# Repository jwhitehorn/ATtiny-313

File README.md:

#Overview

Open design for a ATtiny2313/4313 development platform.

Inspired by:

[BB-313](http://www.johngineer.com/projects/bb313/)

#License
Designs copyright 2013, Jason Whitehorn released under the terms of:

[Creative Commons CC-BY-SA 3.0](http://creativecommons.org/licenses/by-sa/3.0/us/)

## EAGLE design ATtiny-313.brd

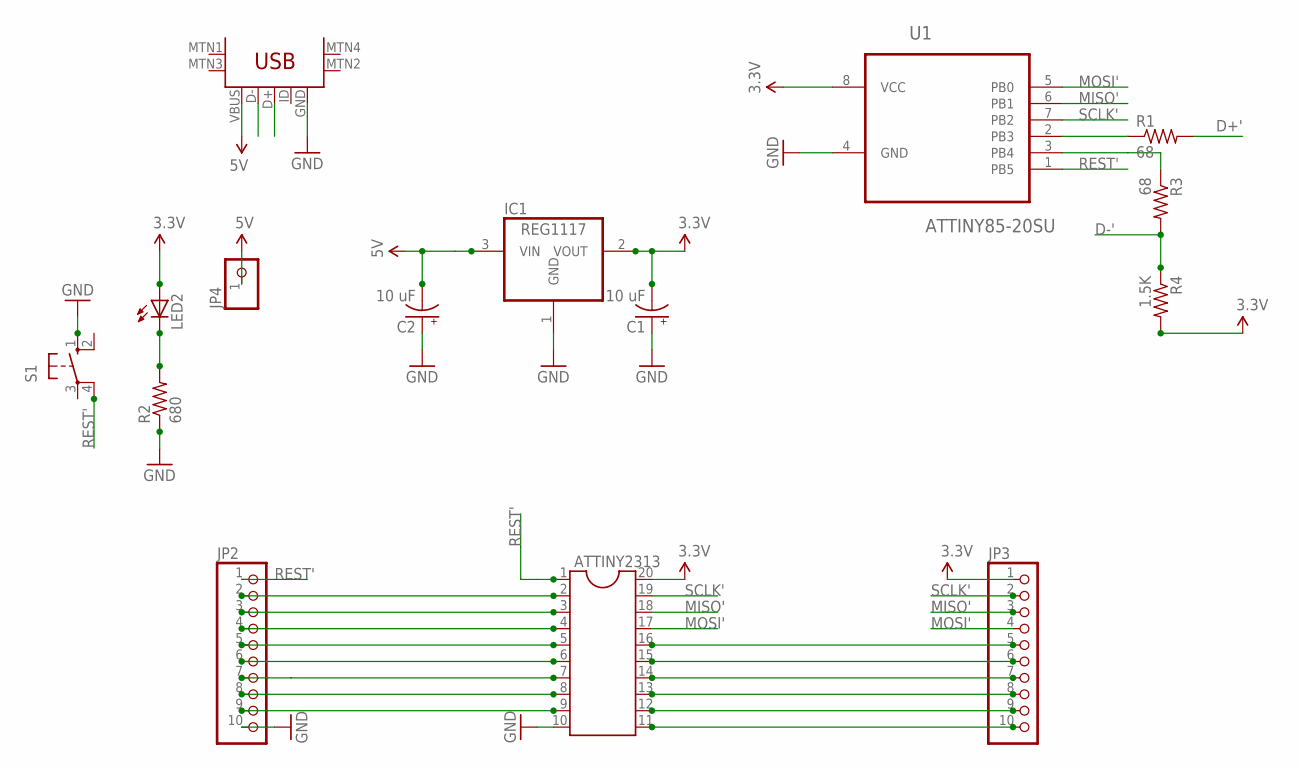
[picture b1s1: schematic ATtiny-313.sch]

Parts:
ATTINY2313: DIL20S; SOCKET-20
C1, C2: 10 uF; E1,8-4
IC1: REG1117; SOT223
JP2, JP3: PINHD-1X10; 1X10
JP4: PINHD-1X1; 1X01
LED2: LEDSMT1206; 1206
R1, R3: 68; R3216
R2: 680; R3216
R4: 1.5K; R3216
S1: 10-XX; B3F-10XX
U1: ATTINY85-20SU; SOIC127P798X216-8N
U$1: USB-MINIB-5PIN; USB-MINIB

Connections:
3.3V: ATTINY2313.20, C1.-, IC1.2 (VOUT), JP3.1, LED2.A, R4.2, U1.8 (VCC)
5V: C2.-, IC1.3 (VIN), JP4.1, U$1.VBUS
D+': R1.2
D-': R3.2, R4.1
GND: ATTINY2313.10, C1.+, C2.+, IC1.1 (GND), JP2.10, R2.1, S1.1 (S), U1.4 (GND), U$1.GND
MISO': ATTINY2313.18, JP3.3, U1.6 (PB1)
MOSI': ATTINY2313.17, JP3.4, U1.5 (PB0)
unnamed: ATTINY2313.2, JP2.2
unnamed: ATTINY2313.3, JP2.3
unnamed: ATTINY2313.4, JP2.4
unnamed: ATTINY2313.5, JP2.5
unnamed: ATTINY2313.6, JP2.6
unnamed: ATTINY2313.7, JP2.7
unnamed: ATTINY2313.8, JP2.8
unnamed: ATTINY2313.9, JP2.9
unnamed: R3.1, U1.3 (PB4)
unnamed: R1.1, U1.2 (PB3)
unnamed: ATTINY2313.16, JP3.5
unnamed: ATTINY2313.15, JP3.6
unnamed: ATTINY2313.14, JP3.7
unnamed: ATTINY2313.13, JP3.8
unnamed: ATTINY2313.12, JP3.9
unnamed: ATTINY2313.11, JP3.10
unnamed: LED2.C, R2.2
REST': ATTINY2313.1, JP2.1, S1.4 (P1), U1.1 (PB5)
SCLK': ATTINY2313.19, JP3.2, U1.7 (PB2)

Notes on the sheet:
REST'
SCLK'
MISO'
MOSI'
D-'
D+'

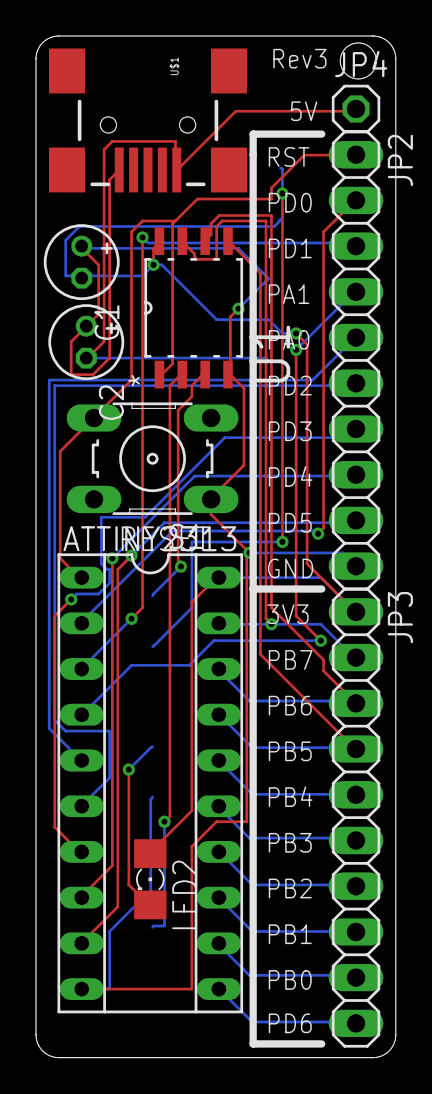
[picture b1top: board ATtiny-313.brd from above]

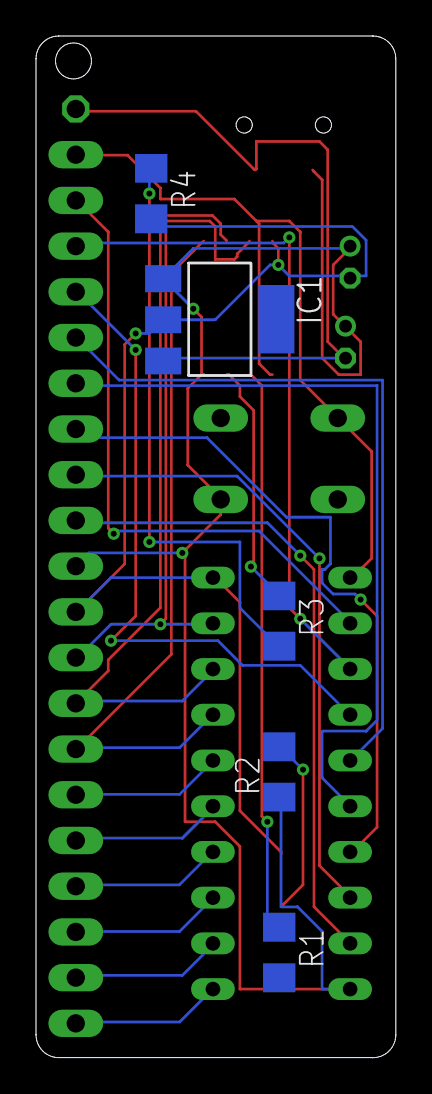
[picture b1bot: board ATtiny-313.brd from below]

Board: 2 copper layers, 20.0 x 56.8 mm, 15 parts (5 on the bottom side), 25 nets.

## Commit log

2013-01-29 added link and OSHW logo
2013-01-29 added readme
2013-01-29 given some credit
2013-01-29 more robust gitignore
2013-01-29 added image
2013-01-29 fixed image
2013-01-29 use SMD to tighten up design
2013-01-29 more SMD goodness
2013-01-29 routing
2013-02-02 tightened up the design
2013-02-03 added built in ISP
2013-02-03 run ISP off 3.3v
2013-02-10 work on rev 3
2013-02-10 added some shots of the assembled revision 2 board
2013-02-10 updated photos in readme
2013-02-10 tweaks to rev 3 board

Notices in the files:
parts and their libraries:
SparkFun-Connectors: Licensing: CC v3.0 Share-Alike You are welcome to use this library for commercial purposes.
